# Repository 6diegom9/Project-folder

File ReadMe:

Publicly disclosed project and templates for various electronics.

Main equipment used with these files:
Ender 3 v2 4.2.2 with bltouch
Arduino IDE with Teensy 4.1 with sd card
labVIEW with arduino Mega and Teensy 4.1 when using labVIEW as a GUI

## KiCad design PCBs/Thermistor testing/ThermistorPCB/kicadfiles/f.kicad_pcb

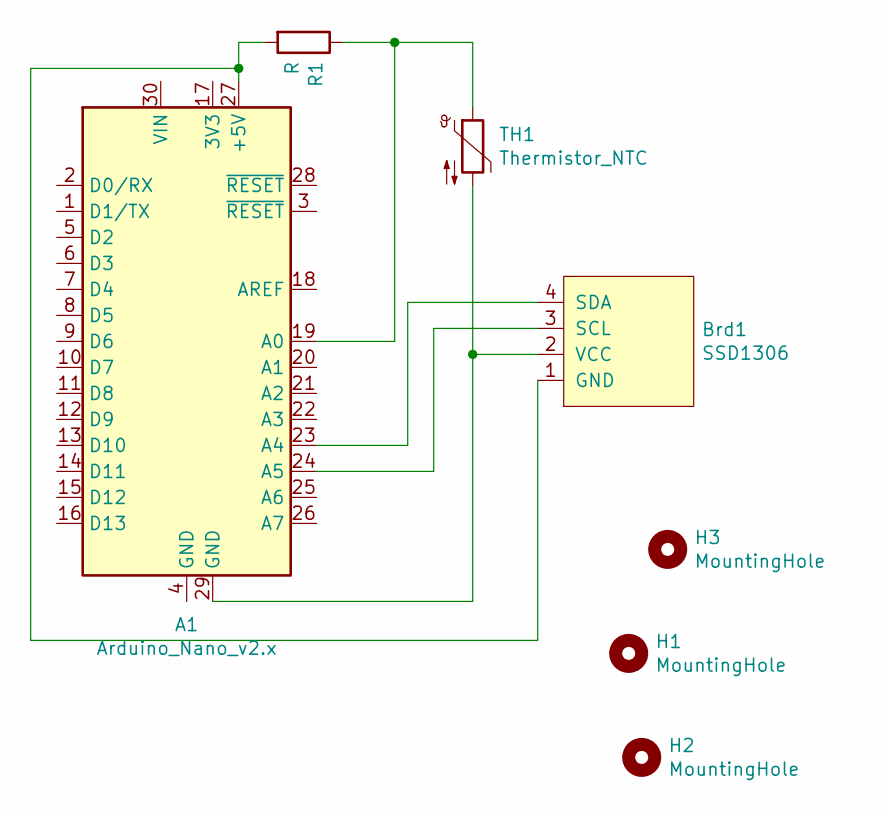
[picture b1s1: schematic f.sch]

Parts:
A1: Arduino_Nano_v2.x; Arduino_Nano
Brd1: SSD1306; PinHeader_1x04_P2.54mm_Vertical
H1, H2, H3: MountingHole; MountingHole_2.5mm
R1: R; R_Axial_DIN0204_L3.6mm_D1.6mm_P5.08mm_Horizontal
TH1: Thermistor_NTC; PinHeader_1x02_P2.54mm_Vertical

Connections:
unnamed: A1.19 (A0), R1.1, TH1.1
unnamed: A1.23 (A4), Brd1.4 (SDA)
unnamed: A1.24 (A5), Brd1.3 (SCL)
unnamed: A1.27 (+5V), Brd1.1 (GND), R1.2
unnamed: A1.29 (GND), Brd1.2 (VCC), TH1.2

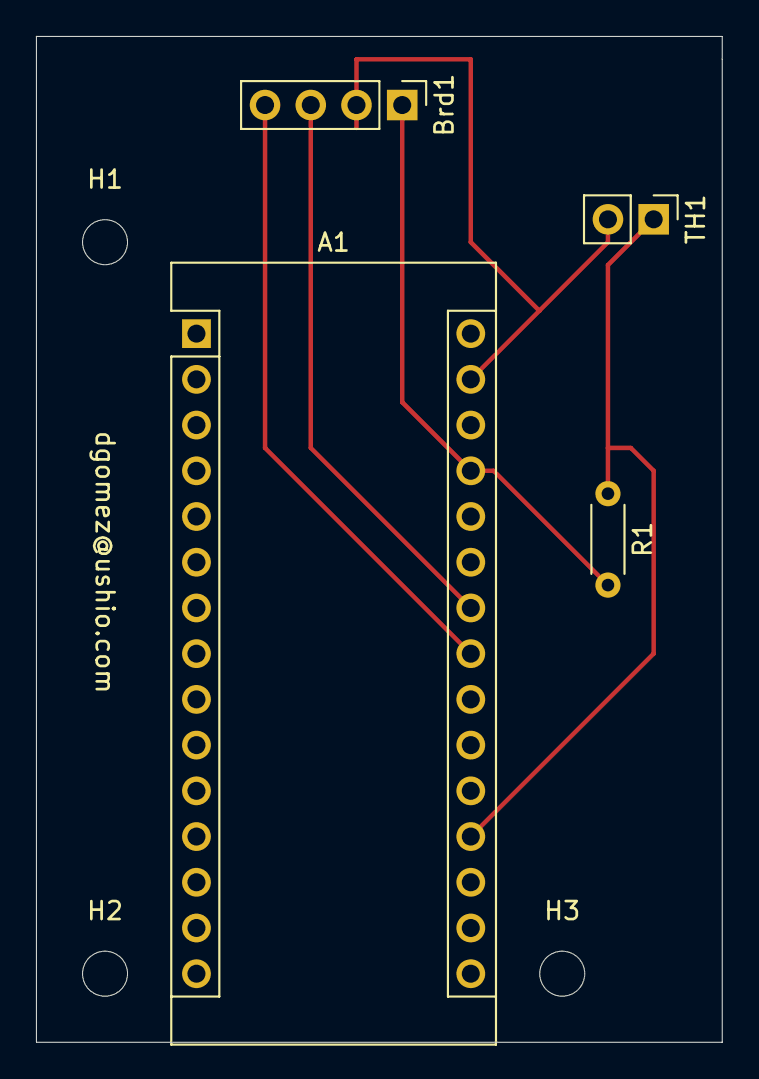
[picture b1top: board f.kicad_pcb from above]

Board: 2 copper layers, 38.1 x 55.9 mm, 7 parts (0 on the bottom side), 5 nets.

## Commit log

2021-04-21 Create progress
2021-04-21 project status
2021-04-21 Arduino Code
    Arduino Code
2021-04-21 Arduino code
2021-04-21 Current and future status
2021-04-22 Arduino code for Teensy 4.1
2021-04-22 No serial communications. For Teensy
2021-04-23 Furnace temp checker
2021-04-23 Using adalogger
2021-04-23 Furnace and setup pics
2021-04-23 Add files via upload
    Ready to test on furnace shown. Meat is cooked inside and covered from the top.
2021-04-23 Pics explained
2021-05-01 Overview
2021-05-01 Self correcting
2021-05-01 Orientation Correction using servo
2021-05-01 project thoughts
2021-05-01 thoughts
2021-05-01 Servo in action
2021-05-18 shifter code
2021-05-18 Shifter code and video
2021-05-18 shifter video
2021-05-18 Notes
2021-06-18 Oozing fix during autolevel
2021-06-18 Oozing fix during bltouch autoleveling
    Waits to heat nozzle until after done autoleveling.
    Also heats 30mm above the bed to prevent clogging.
2021-06-18 Oozing during bltouch autolevel
2021-06-18 readme
2021-06-18 Sensor templates
2021-06-19 Ender 3 v2 bltouch oozing during leveling fix
2021-06-19 Oozing during bltouch and blob during leveling fix
2021-06-26 SG90 servo
2021-06-26 Flight logger
2021-08-14 Blind spot detector
2022-02-28 Add files via upload
    bootleg amazon nano board
2022-03-08 Read
2022-03-16 Roll pitch Yaw on OLED
2022-04-05 photoresistor_to_OLED
2022-04-06 front panel control of arduino pwm
2022-04-07 Labview serial control of an arduino
2022-04-07 labview serial com to arduino pwm
2022-04-14 Thermistor tester
2022-04-14 Thermistor testing prior to soldering
2022-04-24 Thermistor testing device
2022-07-29 Arduino COM Finder subvi
2022-07-29 2020 V Slot Optical Breadboard Attachments
2022-07-29 Low Material Fast Bed Calibration
2022-07-29 Arduino busy port finder
2022-08-01 Confirm information reception
2022-11-16 BL touch, power recovery off, blob squish fix
